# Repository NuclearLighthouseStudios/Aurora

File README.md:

# Aurora Temporal Aliaser

These are the KiCAD schematics and board layout filed for my Aurora Temporal Aliaser.  
If you just want the Gerber files or a PDF of the schematic check out the releases tab for downloads.

This PCB should be easily manufacturable with most online PCB houses by just uploading the gerber files.

This board is designed to be used with my Switchboard Pedal IO PCB which you can find [here](https://github.com/NuclearLighthouseStudios/Switchboard).

## BOM

| Reference | Quantity | Value  | Description                                                     |
| :-------- | -------: | -----: | :-------------------------------------------------------------- |
| C1 C2     | 2        | 100n   | Ceramic disk capacitor                                          |
| C3 C4     | 2        | 100n   | WIMA MKS2 63V                                                   |
| C5        | 1        | 10n    | WIMA MKS2 63V                                                   |
| C6        | 1        | 1µ     | WIMA MKS2 50V                                                   |
| C7        | 1        | 47n    | WIMA MKS2 63V                                                   |
| J1        | 1        |        | Pin Header, 6 pins, 2.54mm spacing                              |
| J2        | 1        |        | DC Barrel Jack with internal switch                             |
| Q1        | 1        | BC547B | 0.1A Ic, 45V Vce, Small Signal NPN Transistor, TO-92:TO-92_Wide |
| Q2        | 1        | J113   | N-JFET transistor, drain/source/gate                            |
| R1 R2 R9  | 3        | 1M     | Metal film resistor 1%, DIN 0207                                |
| R3 R8 R11 | 3        | 1k     | Metal film resistor 1%, DIN 0207                                |
| R4        | 1        | 10k    | Metal film resistor 1%, DIN 0207                                |
| R5 R6 R7  | 3        | 100k   | Metal film resistor 1%, DIN 0207                                |
| R10       | 1        | 47k    | Metal film resistor 1%, DIN 0207                                |
| R12       | 1        | 100    | Metal film resistor 1%, DIN 0207                                |
| RV1       | 1        | 100k   | Alps RK09K1130C94 Potentiometer                                 |
| U1        | 1        | TL072  | Dual Low-Noise JFET-Input Operational Amplifiers, DIP-8/SOIC-8  |
| U2        | 1        | NE555P | Precision Timers, 555 compatible, PDIP-8                        |
|           | 2        |        | 8 pin DIP socket for U1 and U2                                  |

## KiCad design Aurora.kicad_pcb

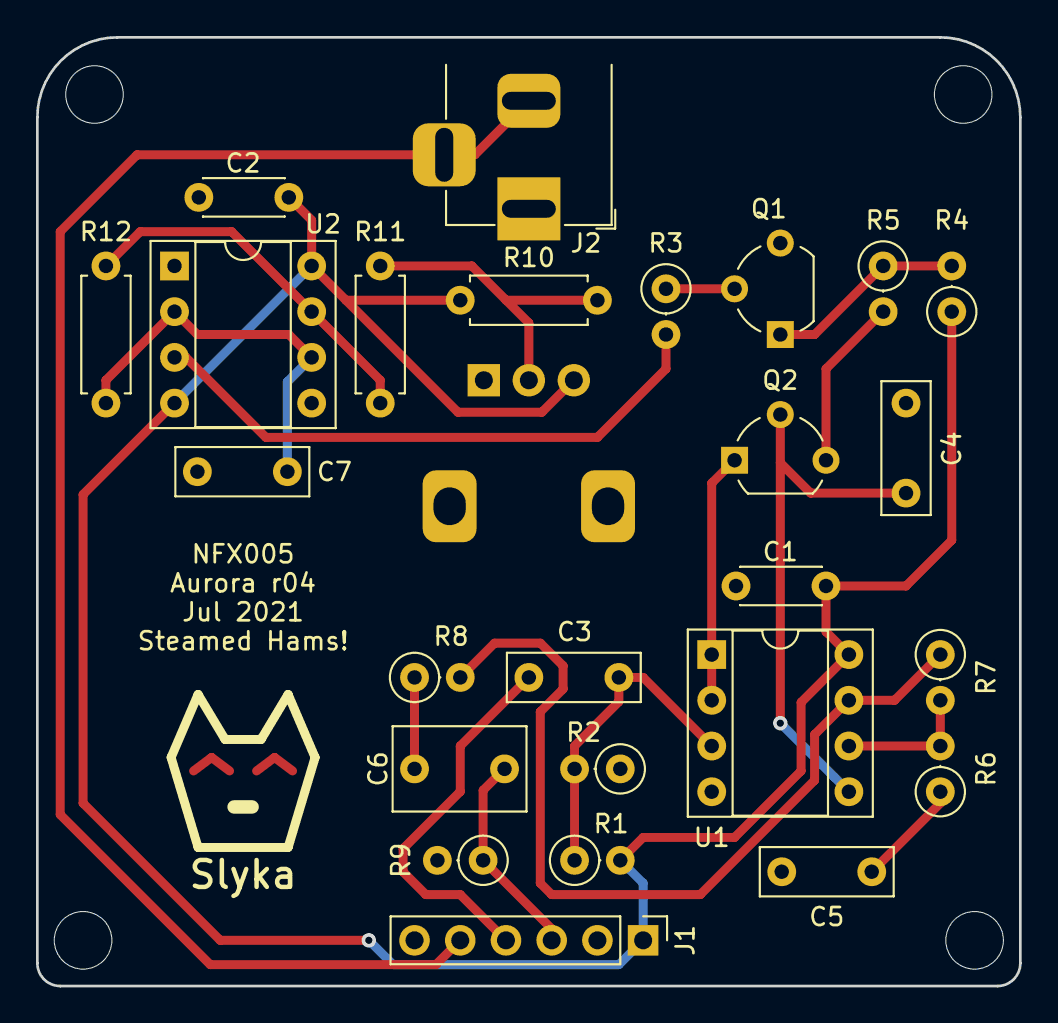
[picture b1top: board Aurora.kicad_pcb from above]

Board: 2 copper layers, 54.6 x 52.7 mm, 26 parts (1 on the bottom side), 19 nets.

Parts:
C1, C2: 100n; C_Disc_D4.3mm_W1.9mm_P5.00mm
C3, C4: 100n; C_Rect_L7.2mm_W2.5mm_P5.00mm_FKS2_FKP2_MKS2_MKP2
C5: 10n; C_Rect_L7.2mm_W2.5mm_P5.00mm_FKS2_FKP2_MKS2_MKP2
C6: 1µ; C_Rect_L7.2mm_W4.5mm_P5.00mm_FKS2_FKP2_MKS2_MKP2
C7: 47n; C_Rect_L7.2mm_W2.5mm_P5.00mm_FKS2_FKP2_MKS2_MKP2
J1: Conn_01x06_Female; PinHeader_1x06_P2.54mm_Vertical
J2: Barrel_Jack_Switch; BarrelJack_Horizontal_Short
Q1: BC547; TO-92_Wide
Q2: J113; TO-92_Wide
R1, R2, R9: 1M; R_Axial_DIN0207_L6.3mm_D2.5mm_P2.54mm_Vertical
R3, R8: 1k; R_Axial_DIN0207_L6.3mm_D2.5mm_P2.54mm_Vertical
R4: 10k; R_Axial_DIN0207_L6.3mm_D2.5mm_P2.54mm_Vertical
R5, R6, R7: 100k; R_Axial_DIN0207_L6.3mm_D2.5mm_P2.54mm_Vertical
R10: 47k; R_Axial_DIN0207_L6.3mm_D2.5mm_P7.62mm_Horizontal
R11: 1k; R_Axial_DIN0207_L6.3mm_D2.5mm_P7.62mm_Horizontal
R12: 100; R_Axial_DIN0207_L6.3mm_D2.5mm_P7.62mm_Horizontal
RV1: 100k; Potentiometer_Alps_RK09K_Single_Vertical
U1: TL072; DIP-8_W7.62mm_Socket
U2: NE555P; DIP-8_W7.62mm_Socket

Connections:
+9V: J1.5, J2.2, J2.3
+9VA: C1.1, C2.1, J1.1, R1.2, R4.1, R10.1, RV1.3, U1.8 (V+), U2.4 (R), U2.8 (VCC)
Clock: R3.2, U2.3 (Q)
GND: C1.2, C2.2, C4.2, C5.2, C7.2, J1.6, J2.1, Q1.3 (E), R2.1, R9.2, U1.4 (V-), U2.1 (GND)
Input: C3.2, J1.4
unnamed: C3.1, R1.1, R2.2, U1.3 (+)
unnamed: C4.1, Q2.2 (S), U1.5 (+)
unnamed: C5.1, R6.1
unnamed: C6.2, R8.1
unnamed: C7.1, R12.1, U2.2 (TR), U2.6 (THR)
unnamed: Q1.1 (C), R4.2, R5.1
unnamed: Q1.2 (B), R3.1
unnamed: Q2.1 (D), U1.1, U1.2 (-)
unnamed: Q2.3 (G), R5.2
unnamed: R6.2, R7.2, U1.6 (-)
unnamed: R7.1, R8.2, U1.7
unnamed: R10.2, R11.2, RV1.2
unnamed: R11.1, R12.2, U2.7 (DIS)
Output: C6.1, J1.3, R9.1

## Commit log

2020-09-28 Initial commit! Whoo!
2020-10-04 Correctly annotate output DC reference resistor and add to PCB
2020-10-04 Bump revision
2020-11-16 Add readme with bom!
2020-11-16 Fix bom formatting
2020-12-31 Fix readme and bom
2020-12-31 Update BOM to latest board revision
2021-03-26 Include sockets for U1 and U2 in BOM
2021-07-04 Properly connect trace between R1 and R2
2021-09-15 Add .svg to gitignore
2022-08-14 Upgrade to KiCAD 6

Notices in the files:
Aurora.kicad_pcb:
CC BY-NC-SA
